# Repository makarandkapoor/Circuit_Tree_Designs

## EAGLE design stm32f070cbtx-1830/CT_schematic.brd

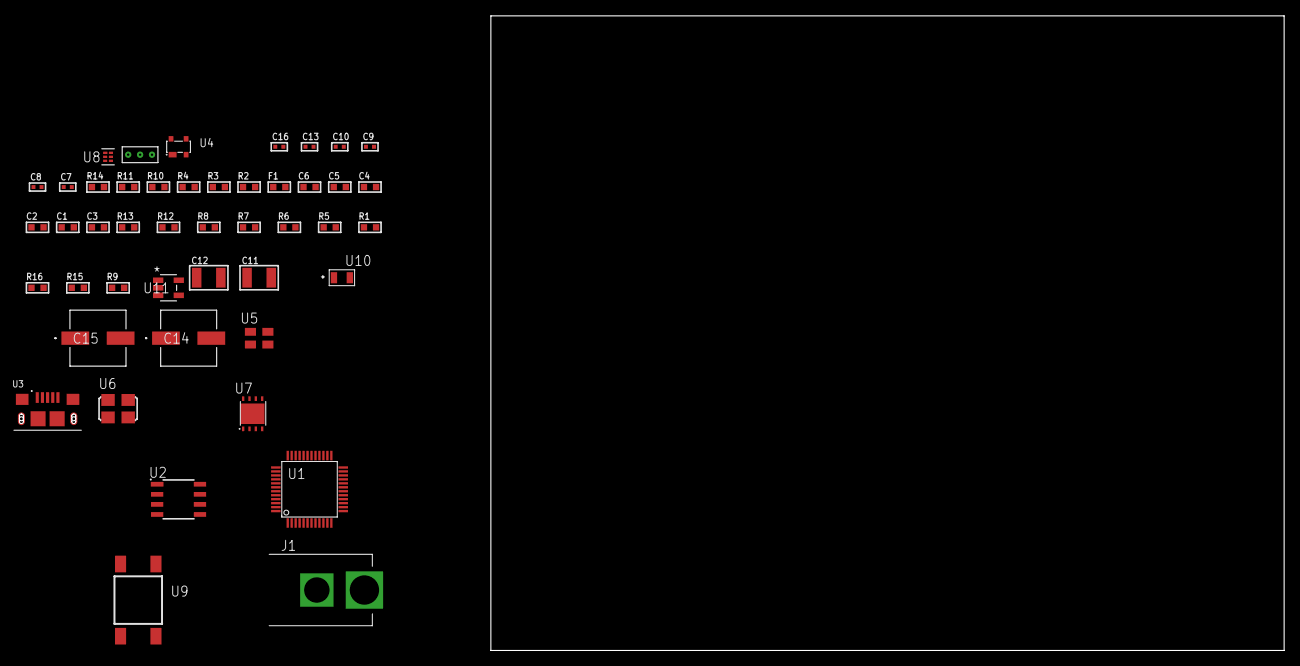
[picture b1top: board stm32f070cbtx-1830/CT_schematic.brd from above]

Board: 2 copper layers, 159.4 x 80.0 mm, 46 parts (0 on the bottom side), 28 nets, no tracks yet.

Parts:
C1, C2, C4: 1e-07; C0603
C3: 4.7e-06; C0603
C5: 1e-08; C0603
C6: 1e-06; C0603
C7, C8, C9, C10, C16: 1e-08; C0402
C11, C12: 1e-05; C1210
C13: 1e-07; C0402
C14, C15: 0.0001; EXV-9H
F1: 240.0; L0603
J1: PJ-037B; PJ-037B_PACKAGE
R1, R5, R6, R7, R8, R12, R13: 10000.0; R0603
R2, R11: 1000.0; R0603
R3: 1600.5; R0603
R4: 4700.0; R0603
R9: 100000.0; R0603
R10: 2231.0; R0603
R14: 9100.0; R0603
R15: 680000.0; R0603
R16: 120000.0; R0603
U1: stm32f070cbt6; LQFP48
U2: AT25080B-SSHL-T; SOIC-8
U3: 10118193-0001LF; FCI_10118193-0001LF
U4: prtr5v0u2ax; SOT143B
U5: ASEK-32.768KHz-ECST; ASEK
U6: ASFL1-25MHZ-NCS; ASFL1
U7: LP3878SDX-ADJ/NOPB; WSON-8
U8: TPS3895ADRYR; SON-6
U9: 4-1437565-2; SW_4-1437565-2
U10: Q65110A2395; LGM67K-G1J2-24-Z
U11: nc7sz125m5x; NC7SZ125M5X
U12: Dummy; DUMMY_PACKAGE_96

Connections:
CLK_U1_3: U1.3, U5.3
CLK_U1_5: U1.5, U6.3
GND: C1.2, C2.2, C3.2, C4.2, C5.2, C6.2, C7.2, C8.2, C9.2, C10.2, C11.2, C12.2, C13.2, C14.2, C15.2, C16.2, J1.2, R2.2, R5.2, R11.2, R14.2, R16.2, U1.8, U1.23, U1.35, U1.47, U2.4, U3.5, U3.6, U3.7, U3.8, U3.9, U4.1, U5.2, U6.2, U7.3, U7.PAD, U8.2, U10.C, U11.1, U11.3, U12.1
NET_U1_7: R4.1, U1.7, U11.4
NET_U1_9: C5.1, C6.1, F1.1, U1.9
NET_U1_44: R5.1, U1.44
NET_U1_45: R3.1, U1.45, U10.A
NET_U1_46: R1.1, U1.46, U9.3, U9.4
NET_U2_3: R6.1, U2.3
NET_U2_7: R8.1, U2.7
NET_U4_4: U3.1, U4.4
NET_U7_1: C10.1, U7.1
NET_U7_6: R10.2, R11.1, U7.6
NET_U7_8: R9.1, U7.8
NET_U8_1: R13.1, R14.1, U8.1
NET_U8_3: R15.2, R16.1, U8.3
NET_U8_4: R12.1, U8.4, U11.2
NET_U9_1: R2.1, U9.1, U9.2
PROC_ADC_IN3: U1.13, U12.2
PROC_ADC_IN9: U1.19, U12.3
PROC_SPI1_MISO: U1.16, U2.2
PROC_SPI1_MOSI: U1.17, U2.5
PROC_SPI1_NSS: R7.1, U1.14, U2.1
PROC_SPI1_SCK: U1.15, U2.6
PROC_USB_DM: U1.32, U3.2, U4.3
PROC_USB_DP: U1.33, U3.3, U4.2
VCC_S1_11V2: C11.1, C14.1, C15.1, J1.1, R9.2, U7.4
VCC_TIER1_3V3: C1.1, C2.1, C3.1, C4.1, C7.1, C8.1, C9.1, C12.1, C13.1, C16.1, F1.2, R1.2, R3.2, R4.2, R6.2, R7.2, R8.2, R10.1, R12.2, R13.2, R15.1, U1.1, U1.24, U1.36, U1.48, U2.8, U5.4, U6.4, U7.5, U8.6, U11.5

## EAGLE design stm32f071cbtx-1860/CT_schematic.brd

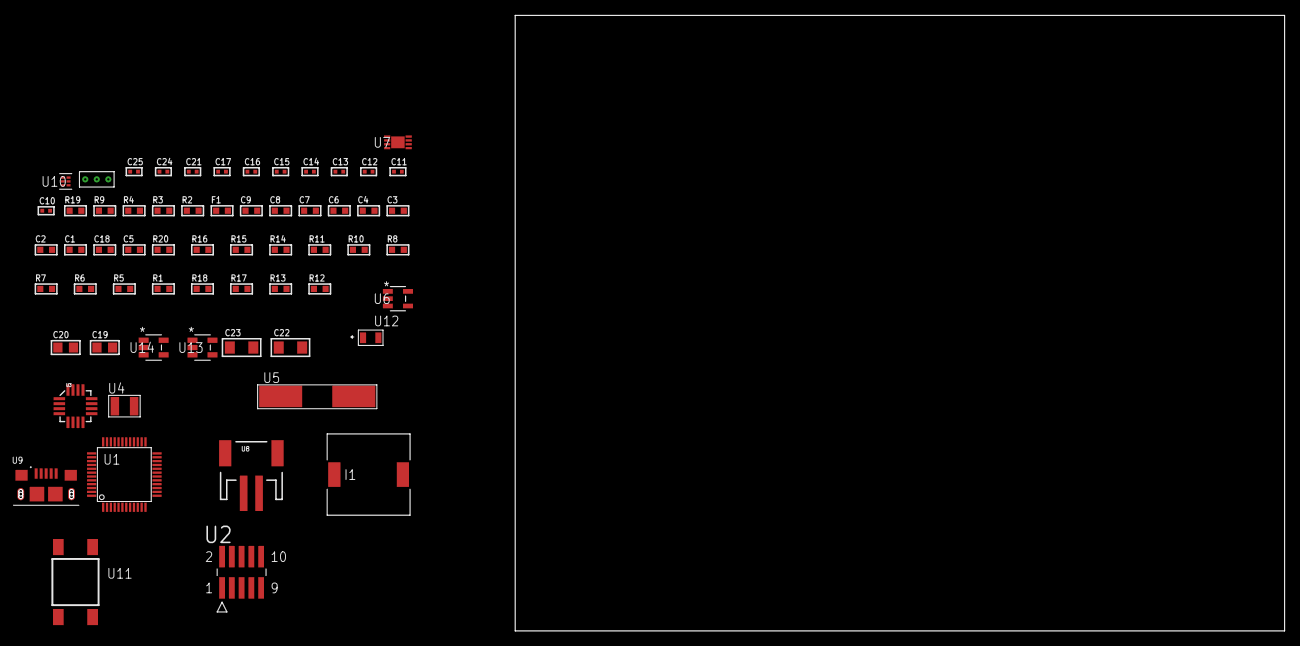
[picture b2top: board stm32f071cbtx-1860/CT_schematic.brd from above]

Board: 2 copper layers, 164.5 x 80.0 mm, 62 parts (0 on the bottom side), 33 nets, no tracks yet.

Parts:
C1, C9: 1e-06; C0603
C2, C3, C4, C6, C7: 1e-07; C0603
C5: 4.7e-06; C0603
C8: 1e-08; C0603
C10, C11, C12, C13: 1e-11; C0402
C14, C21: 1e-07; C0402
C15, C16, C17, C24, C25: 1e-08; C0402
C18: 4.7e-07; C0603
C19, C20: 1e-05; C0805
C22, C23: 1e-05; C1206
F1: 240.0; L0603
I1: 5.2e-06; DR1040
R1, R5, R6, R7, R8, R10, R11, R14, R15, R20: 10000.0; R0603
R2: 1000.0; R0603
R3: 1270.0; R0603
R4: 4700.0; R0603
R9: 5.0; R0603
R12: 309473.68421053; R0603
R13: 1000000.0; R0603
R16: 18000.0; R0603
R17: 470000.0; R0603
R18: 120000.0; R0603
R19: 2000.0; R0603
U1: stm32F071CBT7; LQFP48
U2: FTSH-105-01-L-DV-K; SAMTEC_FTSH-105-01-L-DV-K
U3: l3g4200d; LGA-16
U4: ABS07-32.768KHZ-7-T
U5: ABLS-25.000MHZ-B2F-T
U6: ltc3406es5; TSOT-23-5
U7: MCP73831T-2ACI/MC; DFN8_2X3MC
U8: S2B-PH-SM4-TB(LF)(SN); JST-2-SMD
U9: 10118193-0001LF; FCI_10118193-0001LF
U10: TPS3895ADRYR; SON-6
U11: 4-1437565-2; SW_4-1437565-2
U12: Q65110A2395; LGM67K-G1J2-24-Z
U13, U14: nc7sz125m5x; NC7SZ125M5X
U15: Dummy; DUMMY_PACKAGE_134

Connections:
CLK_CRYSTAL_U1_3: C10.1, U1.3, U4.1
CLK_CRYSTAL_U1_4: C11.1, U1.4, U4.2
CLK_CRYSTAL_U1_5: C12.1, U1.5, U5.1
CLK_CRYSTAL_U1_6: C13.1, U1.6, U5.2
GND: C1.2, C2.2, C3.2, C4.2, C5.2, C6.2, C7.2, C8.2, C9.2, C10.2, C11.2, C12.2, C13.2, C14.2, C15.2, C16.2, C17.2, C19.2, C20.1, C20.2, C21.2, C22.2, C23.2, C24.2, C25.2, R2.2, R5.2, R9.2, R10.1, R10.2, R12.2, R16.2, R18.2, R19.2, U1.8, U1.23, U1.35, U1.47, U2.3, U2.5, U3.8, U3.9, U3.10, U3.11, U3.12, U3.13, U6.2, U7.6, U7.9, U8.2, U9.5, U9.6, U9.7, U9.8, U9.9, U10.2, U12.C, U13.2, U13.3, U14.1, U14.3, U15.1
INPUT_USBPOWER_5V: C22.1, R20.2, U7.1, U7.2, U9.1
NET_U1_7: R4.1, U1.7, U14.4
NET_U1_9: C8.1, C9.1, F1.1, U1.9
NET_U1_44: R5.1, U1.44
NET_U1_45: R3.1, U1.45, U12.A
NET_U1_46: R1.1, U1.46, U11.3, U11.4
NET_U2_9: R9.1, U2.9
NET_U3_14: C17.1, C18.1, U3.14
NET_U6_3: I1.1, U6.3
NET_U6_5: R12.1, R13.1, U6.5
NET_U6_ATNET_3: I1.2, R13.2
NET_U7_5: R20.1, U7.5
NET_U7_8: R19.1, U7.8
NET_U10_1: R15.1, R16.1, U10.1
NET_U10_3: R17.2, R18.1, U10.3
NET_U10_4: R14.1, U10.4, U13.4, U14.2
NET_U11_1: R2.1, U11.1, U11.2
PROC_PA0: U1.10, U15.3
PROC_PC13: U1.2, U15.2
PROC_SPI1_MISO: U1.16, U3.4
PROC_SPI1_MOSI: U1.17, U3.3
PROC_SPI1_NSS: R11.1, U1.14, U3.5
PROC_SPI1_SCK: U1.15, U3.2
PROC_SYS_SWCLK: R7.1, U1.37, U2.4
PROC_SYS_SWDIO: R8.1, U1.34, U2.2
RST_OUT_U2_JTAG_RST_B: R6.1, U2.10, U13.1
VCC_S1_3V7: C19.1, C23.1, U6.4, U7.3, U7.4, U8.1
VCC_TIER1_2V5: C1.1, C2.1, C3.1, C4.1, C5.1, C6.1, C7.1, C14.1, C15.1, C16.1, C20.2, C21.1, C24.1, C25.1, F1.2, I1.2, R1.2, R3.2, R4.2, R6.2, R7.2, R8.2, R11.2, R13.2, R14.2, R15.2, R17.1, U1.1, U1.24, U1.36, U1.48, U2.1, U3.1, U3.15, U3.16, U10.6, U13.5, U14.5

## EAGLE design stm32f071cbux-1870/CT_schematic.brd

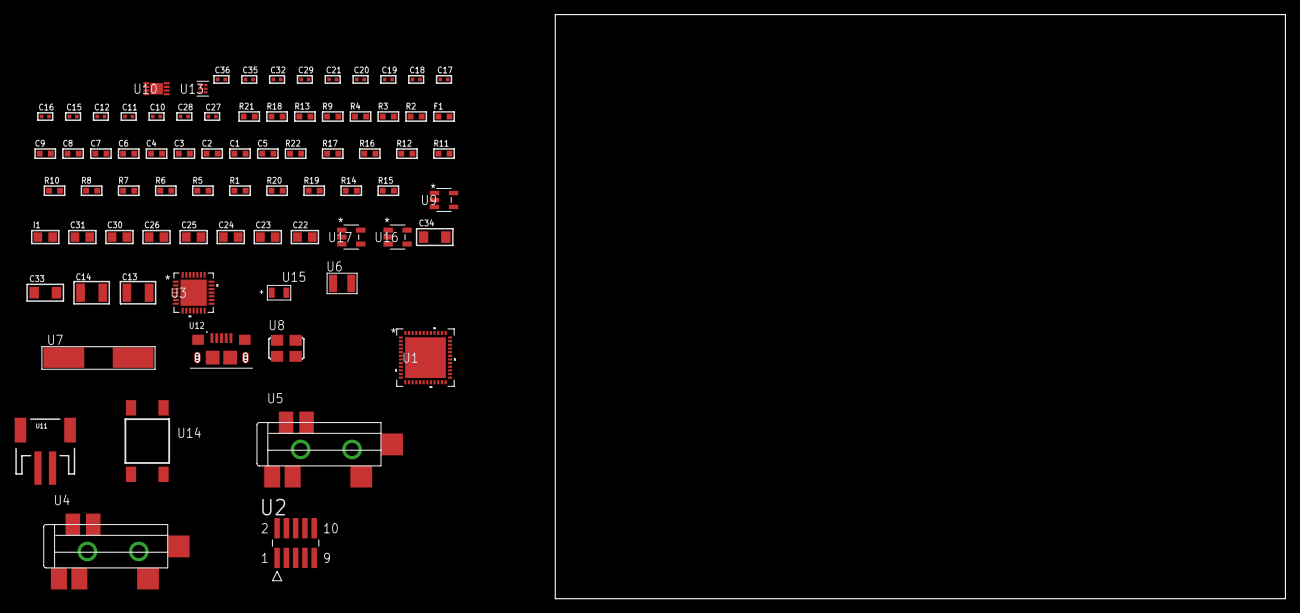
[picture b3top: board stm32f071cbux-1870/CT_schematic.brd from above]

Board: 2 copper layers, 77 parts (0 on the bottom side), 34 nets, no tracks yet.

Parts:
C1, C9: 1e-06; C0603
C2, C3, C4, C6, C7: 1e-07; C0603
C5: 4.7e-06; C0603
C8: 1e-08; C0603
C10, C11: 1e-11; C0402
C12, C17, C18, C19, C20, C21, C32: 1e-07; C0402
C13, C14: 2.2e-05; C1210
C15, C16: 1e-09; C0402
C22, C23, C24, C25, C26, C30, C31: 1e-05; C0805
C27, C28: 2.2e-11; C0402
C29, C35, C36: 1e-08; C0402
C33, C34: 1e-05; C1206
F1: 240.0; L0603
I1: 2.2e-06; L0805
R1, R5, R6, R7, R8, R16, R17, R22: 10000.0; R0603
R2: 1000.0; R0603
R3: 1600.5; R0603
R4: 4700.0; R0603
R9: 5.0; R0603
R10, R11, R12: 47000.0; R0603
R13: 680.0; R0603
R14: 220000.0; R0603
R15: 1000000.0; R0603
R18: 9100.0; R0603
R19: 680000.0; R0603
R20: 120000.0; R0603
R21: 2000.0; R0603
U1: stm32f071cbu7; UFQFPN48
U2: FTSH-105-01-L-DV-K; SAMTEC_FTSH-105-01-L-DV-K
U3: WM8731CLSEFL; QFN-28
U4, U5: SJ-43515TS-SMT-TR
U6: ABS07-32.768KHZ-7-T
U7: ABLS-12.288MHZ-B4-T
U8: ASFL1-25MHZ-NCS; ASFL1
U9: ltc3406es5; TSOT-23-5
U10: MCP73831T-2ACI/MC; DFN8_2X3MC
U11: S2B-PH-SM4-TB(LF)(SN); JST-2-SMD
U12: 10118193-0001LF; FCI_10118193-0001LF
U13: TPS3895ADRYR; SON-6
U14: 4-1437565-2; SW_4-1437565-2
U15: Q65110A2395; LGM67K-G1J2-24-Z
U16, U17: nc7sz125m5x; NC7SZ125M5X

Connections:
CLK_CRYSTAL_U1_3: C10.1, U1.3, U6.1
CLK_CRYSTAL_U1_4: C11.1, U1.4, U6.2
CLK_CRYSTAL_U3_1: C27.1, U3.1, U7.1
CLK_CRYSTAL_U3_2: C28.1, U3.2, U7.2
CLK_U1_5: U1.5, U8.3
GND: C1.2, C2.2, C3.2, C4.2, C5.2, C6.2, C7.2, C8.2, C9.2, C10.2, C11.2, C12.2, C16.2, C17.2, C18.2, C19.2, C20.2, C21.2, C22.2, C23.2, C24.2, C25.2, C26.2, C27.2, C28.2, C29.2, C30.2, C31.1, C31.2, C32.2, C33.2, C34.2, C35.2, C36.2, R2.2, R5.2, R9.2, R10.2, R11.2, R12.2, R14.2, R18.2, R20.2, R21.2, U1.8, U1.23, U1.35, U1.47, U1.49, U2.3, U2.5, U3.4, U3.15, U3.19, U3.25, U3.26, U3.29, U4.1, U5.1, U8.2, U9.2, U10.6, U10.9, U11.2, U12.5, U12.6, U12.7, U12.8, U12.9, U13.2, U15.C, U16.2, U16.3, U17.1, U17.3
INPUT_USBPOWER_5V: C33.1, R22.2, U10.1, U10.2, U12.1
NET_U1_7: R4.1, U1.7, U17.4
NET_U1_9: C8.1, C9.1, F1.1, U1.9
NET_U1_44: R5.1, U1.44
NET_U1_45: R3.1, U1.45, U15.A
NET_U1_46: R1.1, U1.46, U14.3, U14.4
NET_U2_9: R9.1, U2.9
NET_U3_20: C21.1, C26.1, U3.20
NET_U4_2: C14.1, R11.1, U4.2
NET_U4_5: C13.1, R10.1, U4.5
NET_U5_5: C15.1, C16.1, R12.1, R13.1, U5.5
NET_U9_3: I1.1, U9.3
NET_U9_5: R14.1, R15.1, U9.5
NET_U9_ATNET_3: I1.2, R15.2
NET_U10_5: R22.1, U10.5
NET_U10_8: R21.1, U10.8
NET_U13_1: R17.1, R18.1, U13.1
NET_U13_3: R19.2, R20.1, U13.3
NET_U13_4: R16.1, U13.4, U16.4, U17.2
NET_U14_1: R2.1, U14.1, U14.2
PROC_I2S1_CK: U1.15, U3.7
PROC_I2S1_SD: U1.17, U3.8
PROC_I2S1_WS: U1.14, U3.9, U3.11
PROC_SYS_SWCLK: R7.1, U1.37, U2.4
PROC_SYS_SWDIO: R8.1, U1.34, U2.2
RST_OUT_U2_JTAG_RST_B: R6.1, U2.10, U16.1
VCC_S1_3V7: C30.1, C34.1, U9.4, U10.3, U10.4, U11.1
VCC_TIER1_3V3: C1.1, C2.1, C3.1, C4.1, C5.1, C6.1, C7.1, C12.1, C17.1, C18.1, C19.1, C20.1, C22.1, C23.1, C24.1, C25.1, C29.1, C31.2, C32.1, C35.1, C36.1, F1.2, I1.2, R1.2, R3.2, R4.2, R6.2, R7.2, R8.2, R15.2, R16.2, R17.2, R19.1, U1.1, U1.24, U1.36, U1.48, U2.1, U3.3, U3.5, U3.12, U3.18, U8.4, U13.6, U16.5, U17.5

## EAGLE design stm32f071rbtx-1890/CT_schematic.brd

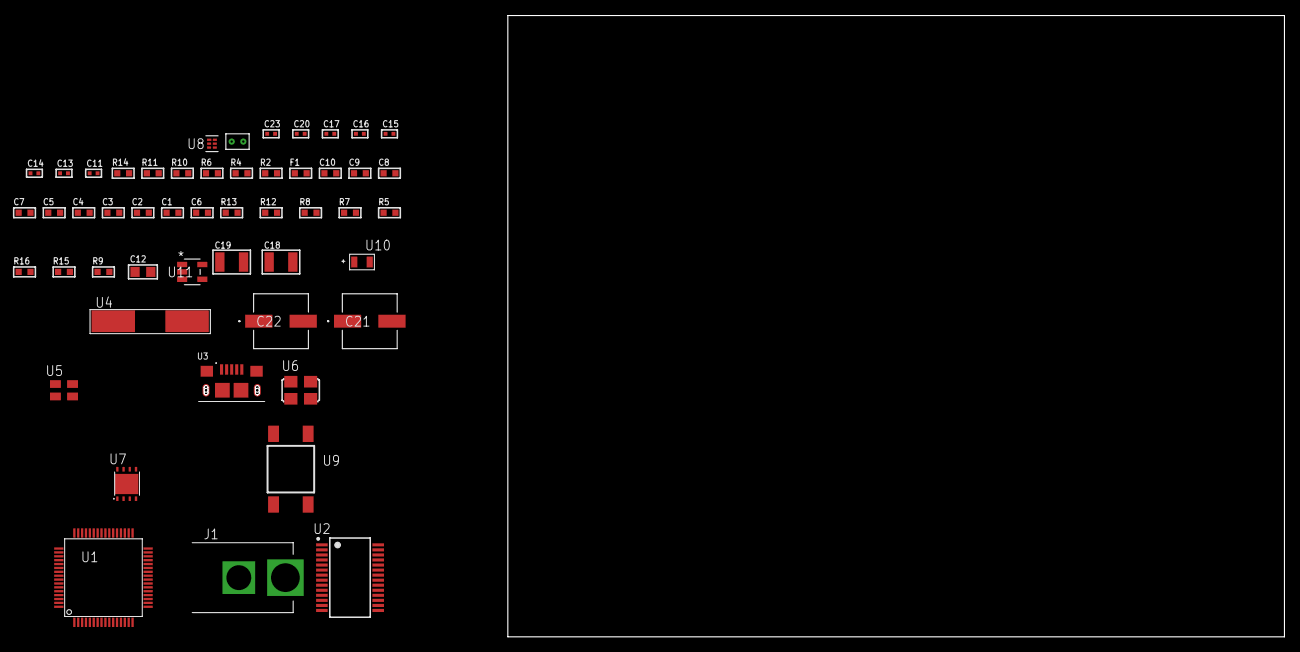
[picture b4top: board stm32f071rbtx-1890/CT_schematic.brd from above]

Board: 2 copper layers, 51 parts (0 on the bottom side), 29 nets, no tracks yet.

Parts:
C1, C10: 1e-06; C0603
C2, C3, C4, C5, C7, C8: 1e-07; C0603
C6: 4.7e-06; C0603
C9: 1e-08; C0603
C11, C13, C14, C20: 1e-07; C0402
C12: 4.7e-06; C0805
C15, C16, C17, C23: 1e-08; C0402
C18, C19: 1e-05; C1210
C21, C22: 0.0001; EXV-9H
F1: 240.0; L0603
J1: PJ-037B; PJ-037B_PACKAGE
R2, R11: 1000.0; R0603
R4, R6: 4700.0; R0603
R5, R7, R8, R12, R13: 10000.0; R0603
R9: 100000.0; R0603
R10: 2231.0; R0603
R14: 9100.0; R0603
R15: 680000.0; R0603
R16: 120000.0; R0603
U1: stm32f071rbt7; LQFP64
U2: FT232RL-REEL; SSOP-28
U3: 10118193-0001LF; FCI_10118193-0001LF
U4: ABLS-12.000MHZ-B4-T
U5: ASEK-32.768KHz-ECST; ASEK
U6: ASFL1-25MHZ-NCS; ASFL1
U7: LP3878SDX-ADJ/NOPB; WSON-8
U8: TPS3895ADRYR; SON-6
U9: 4-1437565-2; SW_4-1437565-2
U10: Q65110A2395; LGM67K-G1J2-24-Z
U11: nc7sz125m5x; NC7SZ125M5X
U12: Dummy; DUMMY_PACKAGE_108

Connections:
CLK_CRYSTAL_U2_27: U2.27, U4.1
CLK_CRYSTAL_U2_28: U2.28, U4.2
CLK_U1_3: U1.3, U5.3
CLK_U1_5: U1.5, U6.3
GND: C1.2, C2.2, C3.2, C4.2, C5.2, C6.2, C7.2, C8.2, C9.2, C10.2, C11.2, C12.2, C13.2, C14.2, C15.2, C16.2, C17.2, C18.2, C19.2, C20.2, C21.2, C22.2, C23.2, J1.2, R2.2, R5.2, R8.2, R11.2, R14.2, R16.2, U1.12, U1.18, U1.31, U1.47, U1.63, U2.7, U2.18, U2.21, U2.25, U2.26, U3.5, U3.6, U3.7, U3.8, U3.9, U5.2, U6.2, U7.3, U7.PAD, U8.2, U10.C, U11.1, U11.3, U12.1
NET_U1_7: R4.1, U1.7, U11.4
NET_U1_13: C9.1, C10.1, F1.1, U1.13
NET_U1_60: R5.1, U1.60
NET_U1_62: U9.3, U9.4
NET_U2_14: R7.1, U2.14
NET_U2_17: C13.1, U2.17
NET_U2_19: R8.1, U2.19
NET_U3_1: R6.1, U3.1
NET_U3_2: U2.16, U3.2
NET_U3_3: U2.15, U3.3
NET_U7_1: C17.1, U7.1
NET_U7_6: R10.2, R11.1, U7.6
NET_U7_8: R9.1, U7.8
NET_U8_1: R13.1, R14.1, U8.1
NET_U8_3: R15.2, R16.1, U8.3
NET_U8_4: R12.1, U8.4, U11.2
NET_U9_1: R2.1, U9.1, U9.2
PROC_DAC_OUT2: U1.21, U12.2
PROC_USART1_CTS: U1.44, U2.3
PROC_USART1_RTS: U1.45, U2.11
PROC_USART1_RX: U1.43, U2.1
PROC_USART1_TX: U1.42, U2.5
VCC_S1_12V0: C18.1, C21.1, C22.1, J1.1, R9.2, U7.4
VCC_TIER1_3V3: C1.1, C2.1, C3.1, C4.1, C5.1, C6.1, C7.1, C8.1, C11.1, C12.1, C14.1, C15.1, C16.1, C19.1, C20.1, C23.1, F1.2, R4.2, R7.2, R10.1, R12.2, R13.2, R15.1, U1.1, U1.19, U1.32, U1.48, U1.64, U2.4, U2.20, U5.4, U6.4, U7.5, U8.6, U11.5

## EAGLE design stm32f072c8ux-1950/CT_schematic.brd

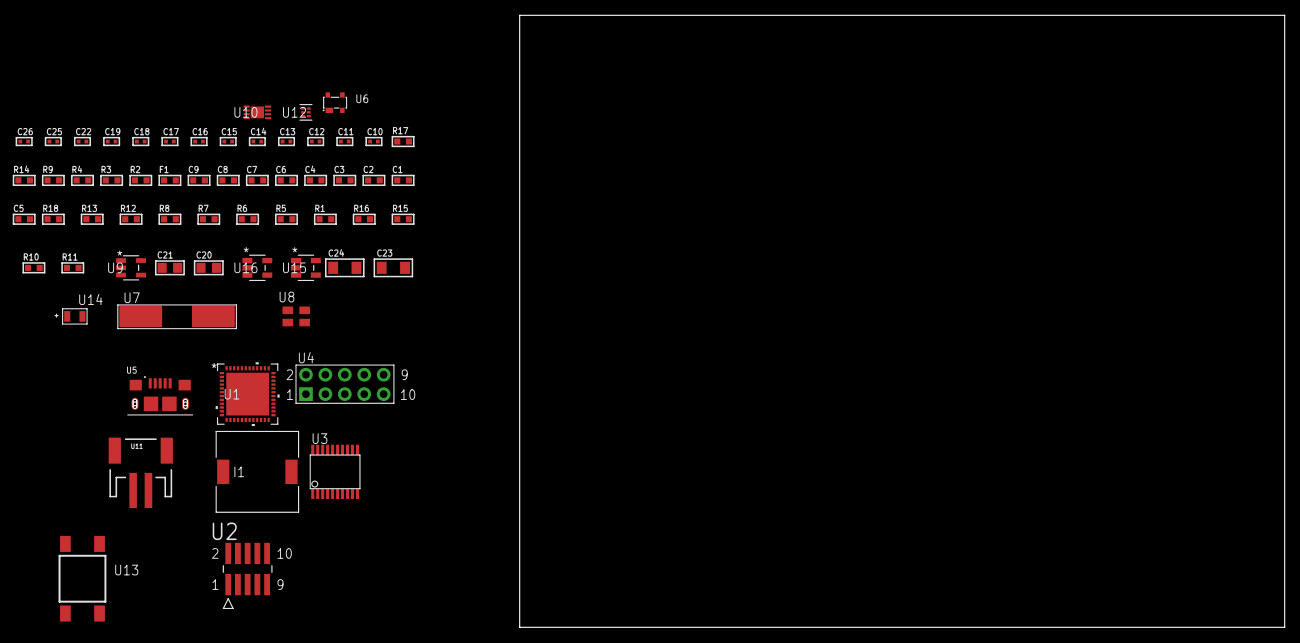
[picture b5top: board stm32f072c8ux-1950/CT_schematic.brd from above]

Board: 2 copper layers, 62 parts (0 on the bottom side), 42 nets, no tracks yet.

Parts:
C1, C9: 1e-06; C0603
C2, C3, C4, C6, C7: 1e-07; C0603
C5: 4.7e-06; C0603
C8: 1e-08; C0603
C10, C11: 1e-11; C0402
C12, C13, C14, C15, C16, C17, C18, C22: 1e-07; C0402
C19, C25, C26: 1e-08; C0402
C20, C21: 1e-05; C0805
C23, C24: 1e-05; C1206
F1: 240.0; L0603
I1: 2.5e-06; DR1040
R1, R5, R6, R7, R8, R12, R13, R18: 10000.0; R0603
R2: 1000.0; R0603
R3: 1600.5; R0603
R4: 4700.0; R0603
R9: 5.0; R0603
R10: 220000.0; R0603
R11: 1000000.0; R0603
R14: 9100.0; R0603
R15: 680000.0; R0603
R16: 120000.0; R0603
R17: 2000.0; R0603
U1: stm32f072c8u6; UFQFPN48
U2: FTSH-105-01-L-DV-K; SAMTEC_FTSH-105-01-L-DV-K
U3: SP3203ECY-L/TR; TSSOP20-I
U4: HTSS-105-01-G-D
U5: 10118193-0001LF; FCI_10118193-0001LF
U6: prtr5v0u2ax; SOT143B
U7: ABLS-25.000MHZ-B2F-T
U8: ASEK-32.768KHz-ECST; ASEK
U9: ltc3406es5; TSOT-23-5
U10: MCP73831T-2ACI/MC; DFN8_2X3MC
U11: S2B-PH-SM4-TB(LF)(SN); JST-2-SMD
U12: TPS3895ADRYR; SON-6
U13: 4-1437565-2; SW_4-1437565-2
U14: Q65110A2395; LGM67K-G1J2-24-Z
U15, U16: nc7sz125m5x; NC7SZ125M5X

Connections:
CLK_CRYSTAL_U1_5: C10.1, U1.5, U7.1
CLK_CRYSTAL_U1_6: C11.1, U1.6, U7.2
CLK_U1_3: U1.3, U8.3
GND: C1.2, C2.2, C3.2, C4.2, C5.2, C6.2, C7.2, C8.2, C9.2, C10.2, C11.2, C12.2, C13.2, C14.2, C17.2, C18.2, C19.2, C20.2, C21.1, C21.2, C22.2, C23.2, C24.2, C25.2, C26.2, R2.2, R5.2, R9.2, R10.2, R14.2, R16.2, R17.2, U1.8, U1.23, U1.35, U1.47, U1.49, U2.3, U2.5, U3.18, U4.9, U5.5, U5.6, U5.7, U5.8, U5.9, U6.1, U8.2, U9.2, U10.6, U10.9, U11.2, U12.2, U14.C, U15.2, U15.3, U16.1, U16.3
INPUT_USBPOWER_5V: C23.1, R18.2, U5.1, U6.4, U10.1, U10.2
NET_U1_7: R4.1, U1.7, U16.4
NET_U1_9: C8.1, C9.1, F1.1, U1.9
NET_U1_36: C7.1, U1.36
NET_U1_44: R5.1, U1.44
NET_U1_45: R3.1, U1.45, U14.A
NET_U1_46: R1.1, U1.46, U13.3, U13.4
NET_U2_9: R9.1, U2.9
NET_U3_1: C15.1, U3.1
NET_U3_2: C17.1, U3.2
NET_U3_3: C15.2, U3.3
NET_U3_4: C16.1, U3.4
NET_U3_5: C16.2, U3.5
NET_U3_6: C18.1, U3.6
NET_U4_3: U3.14, U4.3
NET_U4_4: U3.13, U4.4
NET_U4_5: U3.17, U4.5
NET_U4_6: U3.16, U4.6
NET_U9_3: I1.1, U9.3
NET_U9_5: R10.1, R11.1, U9.5
NET_U9_ATNET_3: I1.2, R11.2
NET_U10_5: R18.1, U10.5
NET_U10_8: R17.1, U10.8
NET_U12_1: R13.1, R14.1, U12.1
NET_U12_3: R15.2, R16.1, U12.3
NET_U12_4: R12.1, U12.4, U15.4, U16.2
NET_U13_1: R2.1, U13.1, U13.2
PROC_SYS_SWCLK: R7.1, U1.37, U2.4
PROC_SYS_SWDIO: R8.1, U1.34, U2.2
PROC_USART2_CTS: U1.10, U3.8
PROC_USART2_RTS: U1.11, U3.10
PROC_USART2_RX: U1.13, U3.11
PROC_USART2_TX: U1.12, U3.7
PROC_USB_DM: U1.32, U5.2, U6.3
PROC_USB_DP: U1.33, U5.3, U6.2
RST_OUT_U2_JTAG_RST_B: R6.1, U2.10, U15.1
VCC_S1_3V7: C20.1, C24.1, U9.4, U10.3, U10.4, U11.1
VCC_TIER1_3V3: C1.1, C2.1, C3.1, C4.1, C5.1, C6.1, C12.1, C13.1, C14.1, C19.1, C21.2, C22.1, C25.1, C26.1, F1.2, I1.2, R1.2, R3.2, R4.2, R6.2, R7.2, R8.2, R11.2, R12.2, R13.2, R15.1, U1.1, U1.24, U1.48, U2.1, U3.12, U3.19, U8.4, U12.6, U15.5, U16.5

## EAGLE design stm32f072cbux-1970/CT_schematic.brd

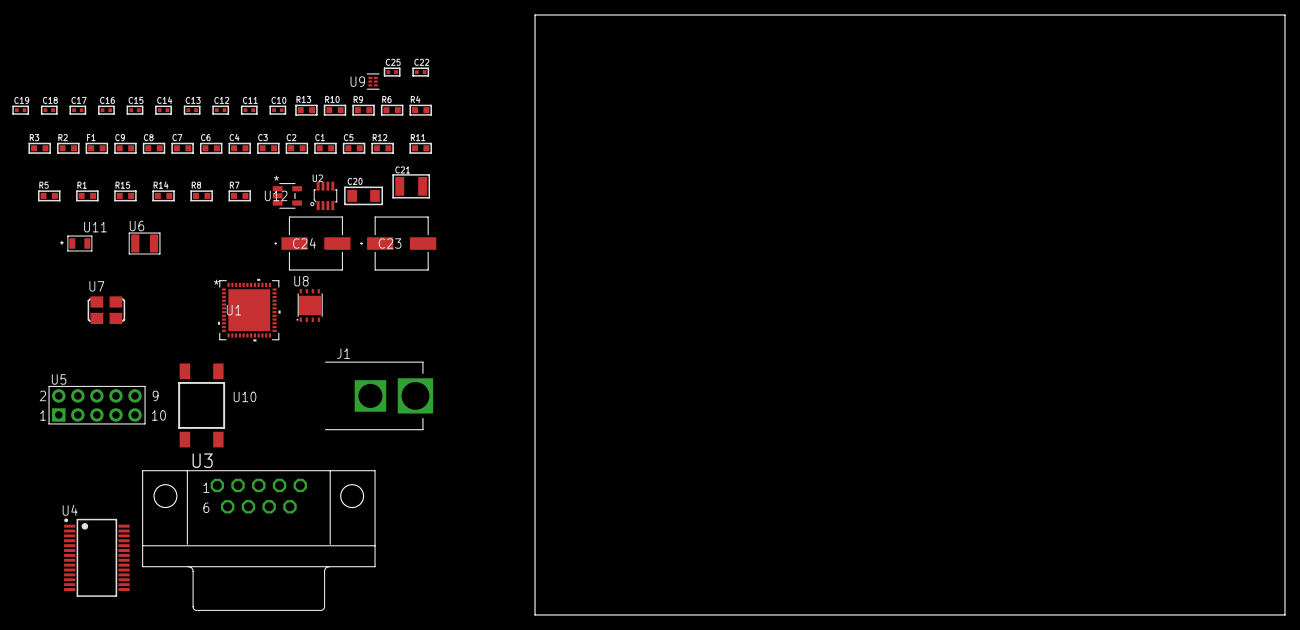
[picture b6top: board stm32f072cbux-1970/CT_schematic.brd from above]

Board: 2 copper layers, 100.0 x 80.0 mm, 54 parts (0 on the bottom side), 38 nets, no tracks yet.

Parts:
C1, C9: 1e-06; C0603
C2, C3, C4, C6, C7: 1e-07; C0603
C5: 4.7e-06; C0603
C8: 1e-08; C0603
C10, C11: 1e-11; C0402
C12, C13, C14, C15, C16, C17, C22: 1e-07; C0402
C18, C19, C25: 1e-08; C0402
C20: 1e-05; C1206
C21: 1e-05; C1210
C23, C24: 0.0001; EXV-9H
F1: 240.0; L0603
J1: PJ-037B; PJ-037B_PACKAGE
R1, R5, R11, R12: 10000.0; R0603
R2, R10: 1000.0; R0603
R3: 1600.5; R0603
R4: 4700.0; R0603
R6: 120.0; R0603
R7, R8: 100000.0; R0603
R9: 2231.0; R0603
R13: 9100.0; R0603
R14: 680000.0; R0603
R15: 120000.0; R0603
U1: stm32f072cbu6; UFQFPN48
U2: MAX3051EKA+T; SOT-23-8
U3: 182-009-113R531; 182-009-MALE
U4: ST3241EBPR; SSOP-28
U5: HTSS-105-01-G-D
U6: ABS07-32.768KHZ-7-T
U7: ASFL1-25MHZ-NCS; ASFL1
U8: LP3878SDX-ADJ/NOPB; WSON-8
U9: TPS3895ADRYR; SON-6
U10: 4-1437565-2; SW_4-1437565-2
U11: Q65110A2395; LGM67K-G1J2-24-Z
U12: nc7sz125m5x; NC7SZ125M5X

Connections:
CLK_CRYSTAL_U1_3: C10.1, U1.3, U6.1
CLK_CRYSTAL_U1_4: C11.1, U1.4, U6.2
CLK_U1_5: U1.5, U7.3
GND: C1.2, C2.2, C3.2, C4.2, C5.2, C6.2, C7.2, C8.2, C9.2, C10.2, C11.2, C12.2, C13.2, C16.2, C17.2, C18.2, C19.2, C20.2, C21.2, C22.2, C23.2, C24.2, C25.2, J1.2, R2.2, R5.2, R10.2, R13.2, R15.2, U1.8, U1.23, U1.35, U1.47, U1.49, U2.2, U2.8, U3.5, U4.23, U4.25, U5.9, U7.2, U8.3, U8.PAD, U9.2, U11.C, U12.1, U12.3
NET_U1_7: R4.1, U1.7, U12.4
NET_U1_9: C8.1, C9.1, F1.1, U1.9
NET_U1_42: R3.1, U1.42, U11.A
NET_U1_43: R1.1, U1.43, U10.3, U10.4
NET_U1_44: R5.1, U1.44
NET_U2_6: R6.2, U2.6
NET_U3_2: R6.2, U2.6, U3.2
NET_U3_3: R6.1, U2.7, U3.3
NET_U4_1: C15.1, U4.1
NET_U4_2: C15.2, U4.2
NET_U4_3: C17.1, U4.3
NET_U4_22: R7.1, U4.22
NET_U4_24: C14.2, U4.24
NET_U4_27: C16.1, U4.27
NET_U4_28: C14.1, U4.28
NET_U5_3: U4.4, U5.3
NET_U5_4: U4.5, U5.4
NET_U5_5: U4.9, U5.5
NET_U5_6: U4.10, U5.6
NET_U8_1: C19.1, U8.1
NET_U8_6: R9.2, R10.1, U8.6
NET_U8_8: R8.1, U8.8
NET_U9_1: R12.1, R13.1, U9.1
NET_U9_3: R14.2, R15.1, U9.3
NET_U9_4: R11.1, U9.4, U12.2
NET_U10_1: R2.1, U10.1, U10.2
PROC_CAN_RX: U1.45, U2.4
PROC_CAN_TX: U1.46, U2.1
PROC_USART1_CTS: U1.32, U4.13
PROC_USART1_RTS: U1.33, U4.18
PROC_USART1_RX: U1.31, U4.19
PROC_USART1_TX: U1.30, U4.14
VCC_S1_8V8: C20.1, C23.1, C24.1, J1.1, R8.2, U8.4
VCC_TIER1_3V3: C1.1, C2.1, C3.1, C4.1, C5.1, C6.1, C7.1, C12.1, C13.1, C18.1, C21.1, C22.1, C25.1, F1.2, R1.2, R3.2, R4.2, R7.2, R9.1, R11.2, R12.2, R14.1, U1.1, U1.24, U1.36, U1.48, U2.3, U4.26, U7.4, U8.5, U9.6, U12.5

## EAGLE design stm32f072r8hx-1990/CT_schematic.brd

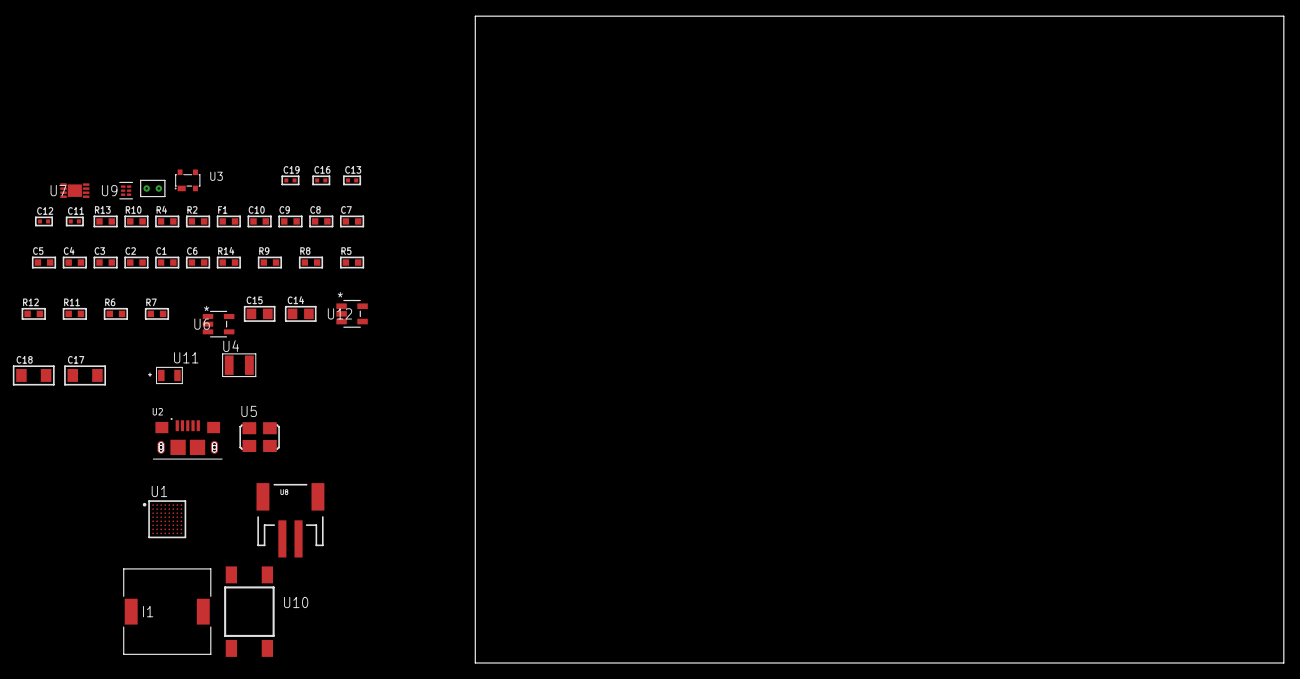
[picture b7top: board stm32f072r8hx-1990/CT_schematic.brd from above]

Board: 2 copper layers, 46 parts (0 on the bottom side), 23 nets, no tracks yet.

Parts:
C1, C10: 1e-06; C0603
C2, C3, C4, C5, C7, C8: 1e-07; C0603
C6: 4.7e-06; C0603
C9: 1e-08; C0603
C11, C12: 1e-11; C0402
C13, C19: 1e-08; C0402
C14, C15: 1e-05; C0805
C16: 1e-07; C0402
C17, C18: 1e-05; C1206
F1: 240.0; L0603
I1: 2.5e-06; DR1040
R2: 1000.0; R0603
R4: 4700.0; R0603
R5, R8, R9, R14: 10000.0; R0603
R6: 220000.0; R0603
R7: 1000000.0; R0603
R10: 9100.0; R0603
R11: 680000.0; R0603
R12: 120000.0; R0603
R13: 2000.0; R0603
U1: stm32f072r8h6; UFBGA64
U2: 10118193-0001LF; FCI_10118193-0001LF
U3: prtr5v0u2ax; SOT143B
U4: ABS07-32.768KHZ-7-T
U5: ASFL1-25MHZ-NCS; ASFL1
U6: ltc3406es5; TSOT-23-5
U7: MCP73831T-2ACI/MC; DFN8_2X3MC
U8: S2B-PH-SM4-TB(LF)(SN); JST-2-SMD
U9: TPS3895ADRYR; SON-6
U10: 4-1437565-2; SW_4-1437565-2
U11: Q65110A2395; LGM67K-G1J2-24-Z
U12: nc7sz125m5x; NC7SZ125M5X
U13: Dummy; DUMMY_PACKAGE_97

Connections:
CLK_CRYSTAL_U1_A1: C11.1, U1.A1, U4.1
CLK_CRYSTAL_U1_B1: C12.1, U1.B1, U4.2
CLK_U1_C1: U1.C1, U5.3
GND: C1.2, C2.2, C3.2, C4.2, C5.2, C6.2, C7.2, C8.2, C9.2, C10.2, C11.2, C12.2, C13.2, C14.2, C15.1, C15.2, C16.2, C17.2, C18.2, C19.2, R2.2, R5.2, R6.2, R10.2, R12.2, R13.2, U1.C2, U1.D4, U1.D5, U1.D6, U1.F1, U2.5, U2.6, U2.7, U2.8, U2.9, U3.1, U5.2, U6.2, U7.6, U7.9, U8.2, U9.2, U11.C, U12.1, U12.3, U13.1
INPUT_USBPOWER_5V: C17.1, R14.2, U2.1, U3.4, U7.1, U7.2
NET_U1_B4: R5.1, U1.B4
NET_U1_E1: R4.1, U1.E1, U12.4
NET_U1_H1: C9.1, C10.1, F1.1, U1.H1
NET_U1_H8: U10.3, U10.4
NET_U6_3: I1.1, U6.3
NET_U6_5: R6.1, R7.1, U6.5
NET_U6_ATNET_3: I1.2, R7.2
NET_U7_5: R14.1, U7.5
NET_U7_8: R13.1, U7.8
NET_U9_1: R9.1, R10.1, U9.1
NET_U9_3: R11.2, R12.1, U9.3
NET_U9_4: R8.1, U9.4, U12.2
NET_U10_1: R2.1, U10.1, U10.2
PROC_DAC_OUT2: U1.F4, U13.2
PROC_USB_DM: U1.C8, U2.2, U3.3
PROC_USB_DP: U1.B8, U2.3, U3.2
VCC_S1_3V7: C14.1, C18.1, U6.4, U7.3, U7.4, U8.1
VCC_TIER1_3V3: C1.1, C2.1, C3.1, C4.1, C5.1, C6.1, C7.1, C8.1, C13.1, C15.2, C16.1, C19.1, F1.2, I1.2, R4.2, R7.2, R8.2, R9.2, R11.1, U1.B2, U1.D2, U1.E4, U1.E5, U1.E6, U5.4, U9.6, U12.5

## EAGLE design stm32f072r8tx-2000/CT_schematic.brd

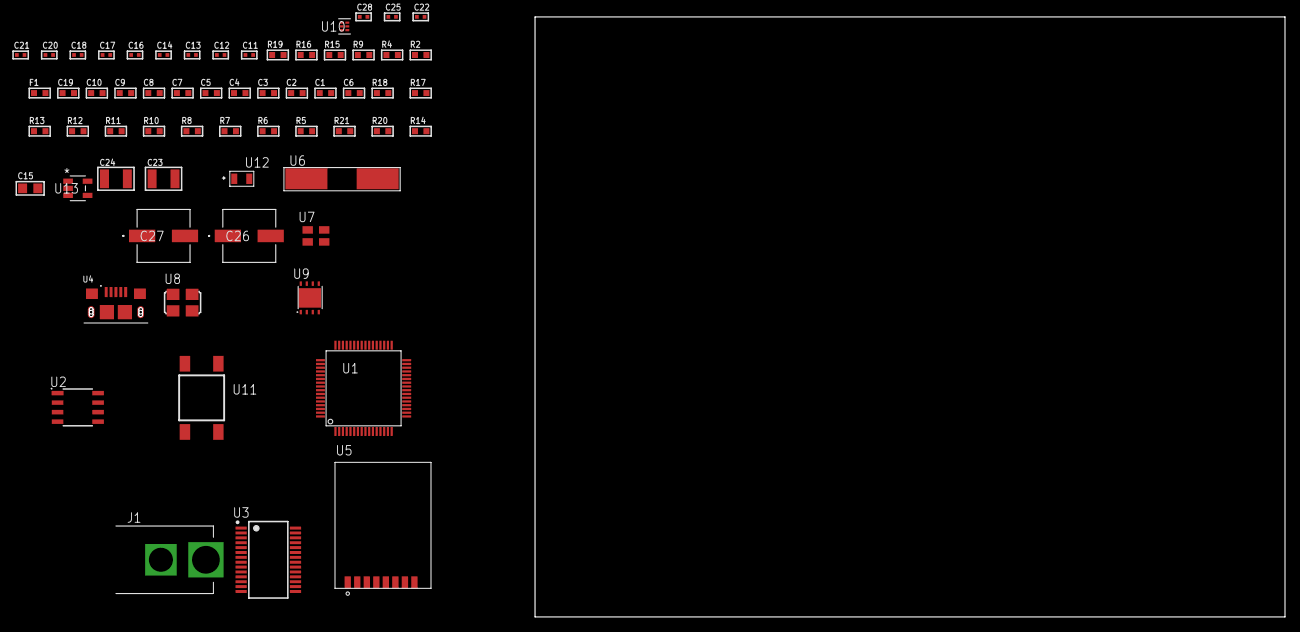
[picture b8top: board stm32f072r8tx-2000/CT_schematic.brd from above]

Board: 2 copper layers, 159.4 x 80.0 mm, 62 parts (0 on the bottom side), 39 nets, no tracks yet.

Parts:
C1, C10, C19: 1e-06; C0603
C2, C3, C4, C5, C7, C8: 1e-07; C0603
C6: 4.7e-06; C0603
C9: 1e-08; C0603
C11, C12: 1e-11; C0402
C13, C20, C21, C22, C28: 1e-08; C0402
C14, C16, C17, C18, C25: 1e-07; C0402
C15: 4.7e-06; C0805
C23, C24: 1e-05; C1210
C26, C27: 0.0001; EXV-9H
F1: 240.0; L0603
J1: PJ-037B; PJ-037B_PACKAGE
R2, R16: 1000.0; R0603
R4, R9: 4700.0; R0603
R5, R6, R7, R8, R10, R11, R12, R13, R17, R18: 10000.0; R0603
R14: 100000.0; R0603
R15: 2231.0; R0603
R19: 9100.0; R0603
R20: 680000.0; R0603
R21: 120000.0; R0603
U1: stm32f072r8t7; LQFP64
U2: AT25020B-SSHL-T; SOIC-8
U3: FT232RL-REEL; SSOP-28
U4: 10118193-0001LF; FCI_10118193-0001LF
U5: RFM75-S
U6: ABLS-25.000MHZ-B2F-T
U7: ASEK-32.768KHz-ECST; ASEK
U8: ASFL1-12MHZ-NCS; ASFL1
U9: LP3878SDX-ADJ/NOPB; WSON-8
U10: TPS3895ADRYR; SON-6
U11: 4-1437565-2; SW_4-1437565-2
U12: Q65110A2395; LGM67K-G1J2-24-Z
U13: nc7sz125m5x; NC7SZ125M5X

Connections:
CLK_CRYSTAL_U1_5: C11.1, U1.5, U6.1
CLK_CRYSTAL_U1_6: C12.1, U1.6, U6.2
CLK_U1_3: U1.3, U7.3
CLK_U3_27: U3.27, U8.3
GND: C1.2, C2.2, C3.2, C4.2, C5.2, C6.2, C7.2, C8.2, C9.2, C10.2, C11.2, C12.2, C13.2, C14.2, C15.2, C16.2, C17.2, C18.2, C19.2, C20.2, C21.2, C22.2, C23.2, C24.2, C25.2, C26.2, C27.2, C28.2, J1.2, R2.2, R5.2, R11.2, R16.2, R19.2, R21.2, U1.12, U1.18, U1.31, U1.47, U1.63, U2.4, U3.7, U3.18, U3.21, U3.25, U3.26, U4.5, U4.6, U4.7, U4.8, U4.9, U5.1, U7.2, U8.2, U9.3, U9.PAD, U10.2, U12.C, U13.1, U13.3
NET_U1_7: R4.1, U1.7, U13.4
NET_U1_13: C9.1, C10.1, F1.1, U1.13
NET_U1_60: R5.1, U1.60
NET_U1_62: U11.3, U11.4
NET_U2_3: R6.1, U2.3
NET_U2_7: R8.1, U2.7
NET_U3_14: R10.1, U3.14
NET_U3_17: C16.1, U3.17
NET_U3_19: R11.1, U3.19
NET_U4_1: R9.1, U4.1
NET_U4_2: U3.16, U4.2
NET_U4_3: U3.15, U4.3
NET_U5_3: R12.1, U5.3
NET_U9_1: C22.1, U9.1
NET_U9_6: R15.2, R16.1, U9.6
NET_U9_8: R14.1, U9.8
NET_U10_1: R18.1, R19.1, U10.1
NET_U10_3: R20.2, R21.1, U10.3
NET_U10_4: R17.1, U10.4, U13.2
NET_U11_1: R2.1, U11.1, U11.2
PROC_SPI1_MISO: U1.22, U5.7
PROC_SPI1_MOSI: U1.23, U5.6
PROC_SPI1_NSS: R13.1, U1.20, U5.4
PROC_SPI1_SCK: U1.21, U5.5
PROC_SPI2_MISO: U1.10, U2.2
PROC_SPI2_MOSI: U1.11, U2.5
PROC_SPI2_NSS: R7.1, U1.33, U2.1
PROC_SPI2_SCK: U1.29, U2.6
PROC_USART1_CTS: U1.44, U3.3
PROC_USART1_RTS: U1.45, U3.11
PROC_USART1_RX: U1.43, U3.1
PROC_USART1_TX: U1.42, U3.5
VCC_S1_15V4: C23.1, C26.1, C27.1, J1.1, R14.2, U9.4
VCC_TIER1_3V3: C1.1, C2.1, C3.1, C4.1, C5.1, C6.1, C7.1, C8.1, C13.1, C14.1, C15.1, C17.1, C18.1, C19.1, C20.1, C21.1, C24.1, C25.1, C28.1, F1.2, R4.2, R6.2, R7.2, R8.2, R10.2, R12.2, R13.2, R15.1, R17.2, R18.2, R20.1, U1.1, U1.19, U1.32, U1.48, U1.64, U2.8, U3.4, U3.20, U5.2, U7.4, U8.4, U9.5, U10.6, U13.5
